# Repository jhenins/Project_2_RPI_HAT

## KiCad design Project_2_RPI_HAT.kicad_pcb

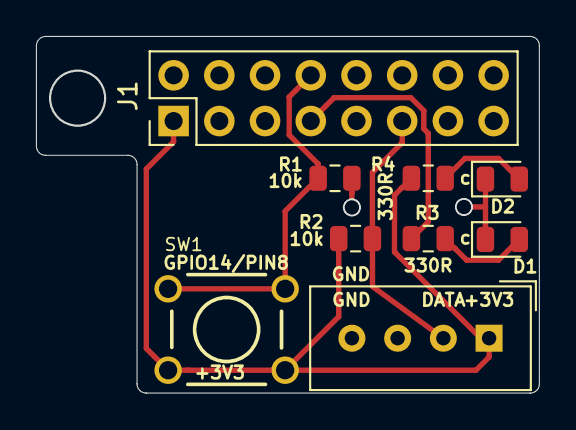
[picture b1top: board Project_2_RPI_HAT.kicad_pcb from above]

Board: 2 copper layers, 27.9 x 19.7 mm, 9 parts (0 on the bottom side), 7 nets.

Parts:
D1, D2: LED; LED_0805_2012Metric
DHT22: DHT22; Aosong_DHT11_5.5x12.0_P2.54mm
J1: Raspberry_Pi_2_3; PinHeader_2x08_P2.54mm_Vertical
R1, R2: 10k; R_0805_2012Metric
R3, R4: 330R; R_0805_2012Metric
SW1: SW_DPST; SW_PUSHBUTTON_PTH

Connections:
+3V3: DHT22.1, J1.1, R2.2, R4.1, SW1.1
/button_input: J1.8, R1.1, SW1.2
GND: D1.1, D2.1, DHT22.4, J1.6, J1.9, R1.2
unnamed: D1.2, R3.2
unnamed: D2.2, R4.2
unnamed: J1.7, R3.1
unnamed: DHT22.2, J1.11, R2.1

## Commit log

2019-10-17 First commint!
